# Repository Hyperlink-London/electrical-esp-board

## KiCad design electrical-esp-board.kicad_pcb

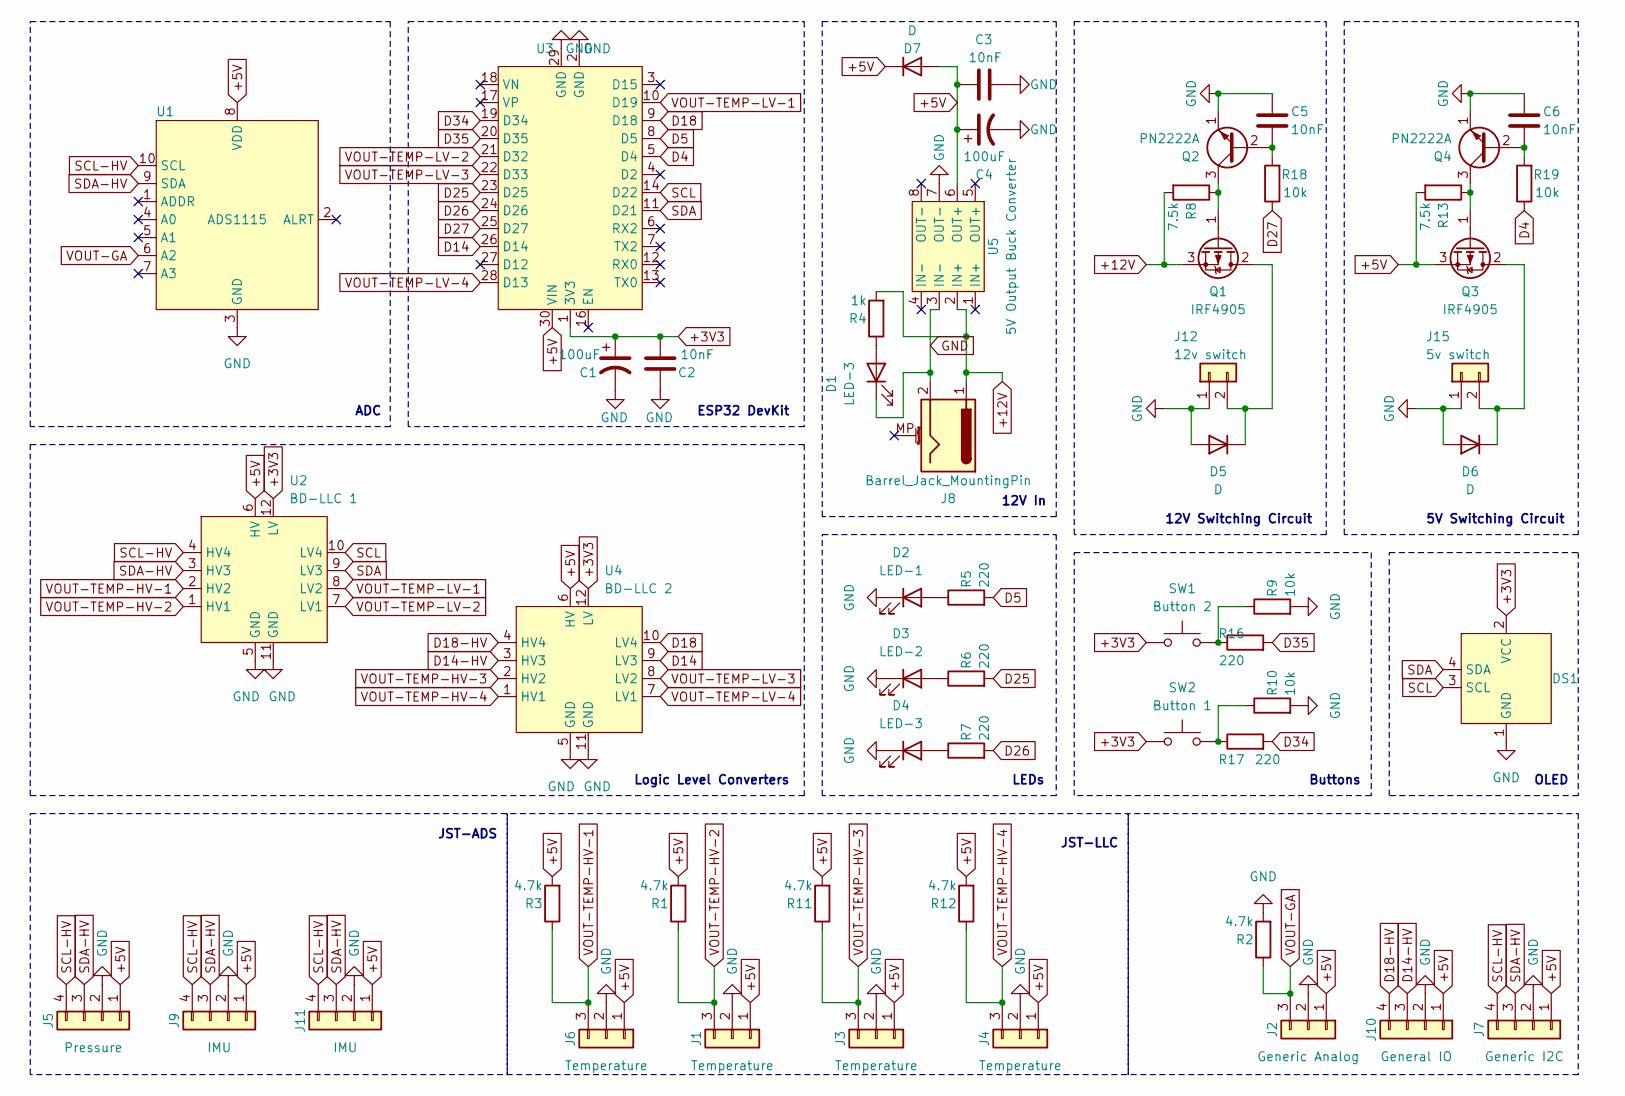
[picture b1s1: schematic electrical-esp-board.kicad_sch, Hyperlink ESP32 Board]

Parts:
C1, C4: 100uF; CP_Radial_D5.0mm_P2.50mm
C2, C3, C5, C6: 10nF; C_Rect_L7.0mm_W3.5mm_P5.00mm
D1, D4: LED-3; LED_D3.0mm
D2: LED-1; LED_D3.0mm
D3: LED-2; LED_D3.0mm
D5, D6, D7: D; D_A-405_P12.70mm_Horizontal
DS1: MODULE_DM-OLED096-636
J1, J3, J4, J6: Temperature; JST_XH_B3B-XH-A_1x03_P2.50mm_Vertical
J2: Generic Analog; JST_XH_B3B-XH-A_1x03_P2.50mm_Vertical
J5: Pressure; JST_XH_B4B-XH-A_1x04_P2.50mm_Vertical
J7: Generic I2C; JST_XH_B4B-XH-A_1x04_P2.50mm_Vertical
J8: Barrel_Jack_MountingPin; BarrelJack_Horizontal
J9, J11: IMU; JST_XH_B4B-XH-A_1x04_P2.50mm_Vertical
J10: General IO; JST_XH_B4B-XH-A_1x04_P2.50mm_Vertical
J12: 12v switch; JST_XH_B2B-XH-A_1x02_P2.50mm_Vertical
J15: 5v switch; JST_XH_B2B-XH-A_1x02_P2.50mm_Vertical
Q1, Q3: IRF4905; TO-220-3_Vertical
Q2, Q4: PN2222A; TO-92_Inline
R1, R2, R3, R11, R12: 4.7k; R_Axial_DIN0204_L3.6mm_D1.6mm_P7.62mm_Horizontal
R4: 1k; R_Axial_DIN0204_L3.6mm_D1.6mm_P7.62mm_Horizontal
R5, R6, R7, R16, R17: 220; R_Axial_DIN0204_L3.6mm_D1.6mm_P7.62mm_Horizontal
R8, R13: 7.5k; R_Axial_DIN0204_L3.6mm_D1.6mm_P7.62mm_Horizontal
R9, R10, R18, R19: 10k; R_Axial_DIN0204_L3.6mm_D1.6mm_P7.62mm_Horizontal
SW1: Button 2; SW_PUSH-12mm_Wuerth-430476085716
SW2: Button 1; SW_PUSH-12mm_Wuerth-430476085716
U1: ADS1115
U2: BD-LLC 1; MODULE_757
U3: MODULE_ESP32_DEVKIT_V1
U4: BD-LLC 2; MODULE_757
U5: 5V Output Buck Converter; 5V-BUCK

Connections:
+3V3: C1.1, C2.1, DS1.2 (VCC), SW1.1, SW2.1, U2.12 (LV), U3.1 (3V3), U4.12 (LV)
+5V: C3.2, C4.1, D7.1 (K), D7.2 (A), J1.1, J2.1, J3.1, J4.1, J5.1, J6.1, J7.1, J9.1, J10.1, J11.1, Q3.3 (S), R1.2, R3.2, R11.2, R12.2, R13.2, U1.8 (VDD), U2.6 (HV), U3.30 (VIN), U4.6 (HV), U5.6 (OUT+)
+12V: J8.1, Q1.3 (S), R4.2, R8.2, U5.2 (IN+)
D4: R19.1, U3.5 (D4)
D5: R5.2, U3.8 (D5)
D14: U3.26 (D14), U4.9 (LV3)
D14-HV: J10.3, U4.3 (HV3)
D18: U3.9 (D18), U4.10 (LV4)
D18-HV: J10.4, U4.4 (HV4)
D25: R6.2, U3.23 (D25)
D26: R7.2, U3.24 (D26)
D27: R18.1, U3.25 (D27)
D34: R17.2, U3.19 (D34)
D35: R16.2, U3.20 (D35)
GND: C1.2, C2.2, C3.1, C4.2, C5.2, C6.2, D1.1 (K), D2.1 (K), D3.1 (K), D4.1 (K), D5.2 (A), D6.2 (A), DS1.1 (GND), J1.2, J2.2, J3.2, J4.2, J5.2, J6.2, J7.2, J8.2, J9.2, J10.2, J11.2, J12.1, J15.1, Q2.1 (E), Q4.1 (E), R2.2, R9.2, R10.2, U1.3 (GND), U2.5 (GND), U2.11 (GND), U3.2 (GND), U3.29 (GND), U4.5 (GND), U4.11 (GND), U5.3 (IN-), U5.7 (OUT-)
unnamed: D1.2 (A), R4.1
unnamed: D2.2 (A), R5.1
unnamed: D3.2 (A), R6.1
unnamed: D4.2 (A), R7.1
unnamed: D5.1 (K), J12.2, Q1.2 (D)
unnamed: D6.1 (K), J15.2, Q3.2 (D)
unnamed: Q1.1 (G), Q2.3 (C), R8.1
unnamed: C5.1, Q2.2 (B), R18.2
unnamed: Q3.1 (G), Q4.3 (C), R13.1
unnamed: C6.1, Q4.2 (B), R19.2
unnamed: R10.1, R17.1, SW2.2
unnamed: R9.1, R16.1, SW1.2
SCL: DS1.3 (SCL), U2.10 (LV4), U3.14 (D22)
SCL-HV: J5.4, J7.4, J9.4, J11.4, U1.10 (SCL), U2.4 (HV4)
SDA: DS1.4 (SDA), U2.9 (LV3), U3.11 (D21)
SDA-HV: J5.3, J7.3, J9.3, J11.3, U1.9 (SDA), U2.3 (HV3)
VOUT-GA: J2.3, R2.1, U1.6 (A2)
VOUT-TEMP-HV-1: J6.3, R3.1, U2.2 (HV2)
VOUT-TEMP-HV-2: J1.3, R1.1, U2.1 (HV1)
VOUT-TEMP-HV-3: J3.3, R11.1, U4.2 (HV2)
VOUT-TEMP-HV-4: J4.3, R12.1, U4.1 (HV1)
VOUT-TEMP-LV-1: U2.8 (LV2), U3.10 (D19)
VOUT-TEMP-LV-2: U2.7 (LV1), U3.21 (D32)
VOUT-TEMP-LV-3: U3.22 (D33), U4.8 (LV2)
VOUT-TEMP-LV-4: U3.28 (D13), U4.7 (LV1)

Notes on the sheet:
12V Switching Circuit
Logic Level Converters
ADC
ESP32 DevKit
JST-ADS
LEDs
JST-LLC
Buttons
12V In
OLED
5V Switching Circuit

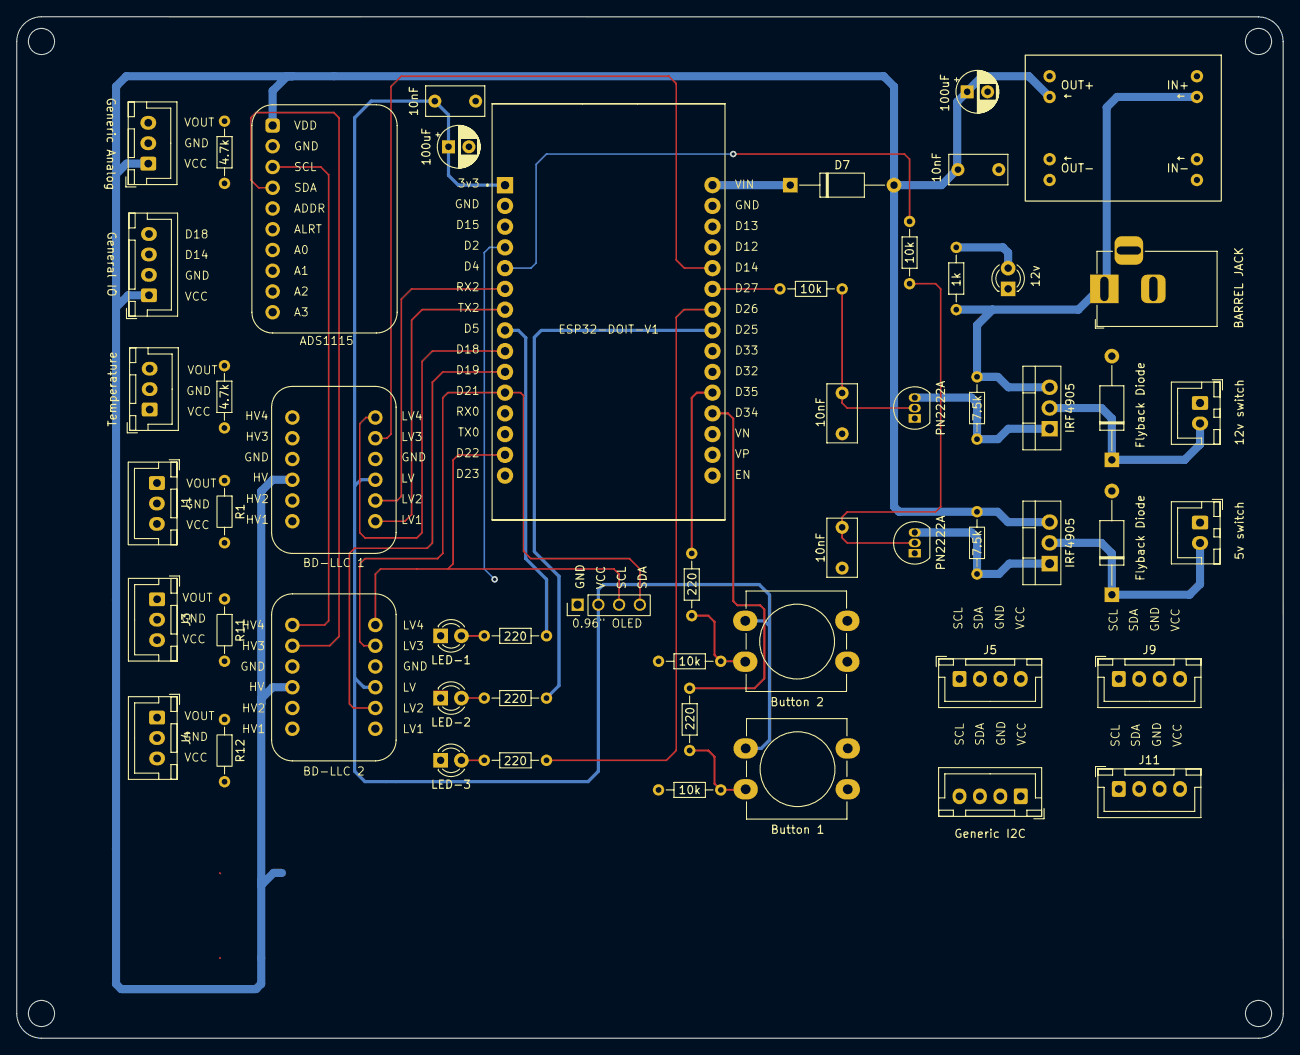
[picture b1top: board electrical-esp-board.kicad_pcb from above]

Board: 2 copper layers, 155.1 x 125.1 mm, 55 parts (0 on the bottom side), 40 nets.

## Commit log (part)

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2025-10-16 inital commit
2025-11-12 removed uneeded JSP pins ready for it to be worked on
2025-11-19 Added edited PCB schematic
    Added:
    3x more temp sensor jsts
    2x IMU / gyro sensor jsts (assumed used I2C)
    1x pressure sensor jst (previous one we found used I2C)
    Yet to add on to the pcb editor
2025-11-19 Fixed redundancy
    Removed unnecessary files that were just for the initial design of the PCB.
2025-12-02 Cleaned up and added rest of JSTs
    removed all of the extra wires and unneeded components. added the footprints of all of the temp sensors and 3 extra I2Cs. aren't in correct position or wired up as of yet
2025-12-02 Moved all JST to proposed locations, unwired
    Moved all of the JSTs to the proposed locations. Waiting to be checked so I can wire it afterwards
2026-01-24 Added extra analogue and another spare I2C JST. Still unwired.
